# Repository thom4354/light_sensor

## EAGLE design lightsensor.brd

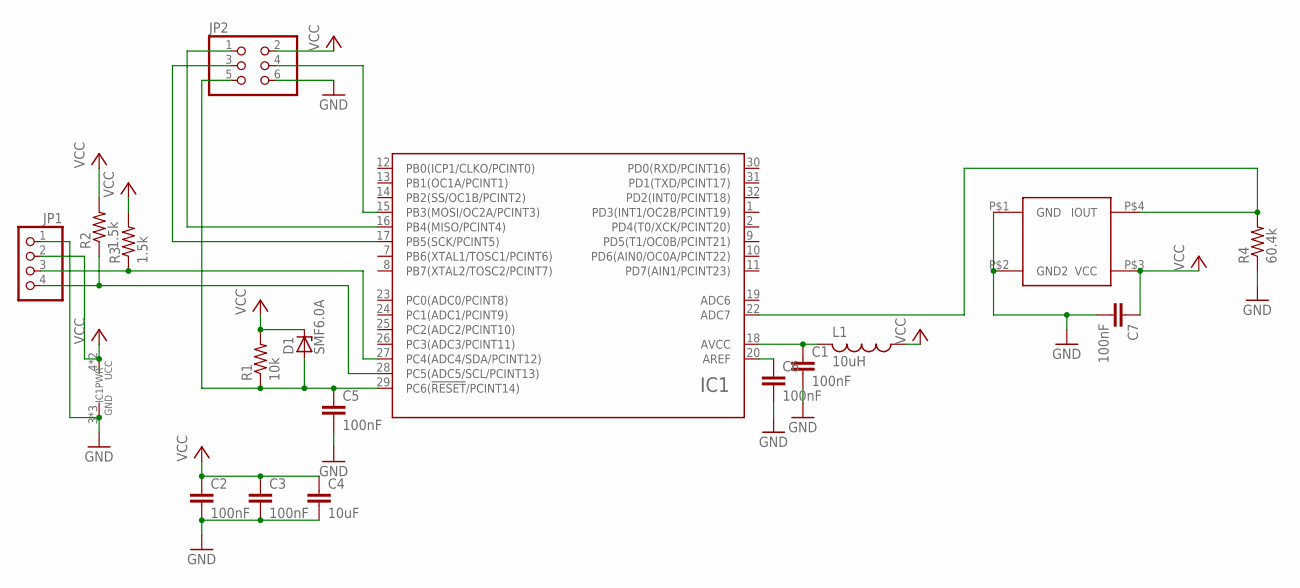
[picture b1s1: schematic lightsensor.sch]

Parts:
C1, C2, C3, C5, C6, C7: 100nF; C0402
C4: 10uF; C0603
D1: SMF6.0A; SOD123F
IC1: ATMEGA48/88/168/328-AU; TQFP32-08
JP1: PINHD-1X4; 1X04
JP2: PINHD-2X3; 2X03
L1: 10uH; L2012C
R1: 10k; R0402
R2, R3: 1.5k; R0402
R4: 60.4k; R0603
U$1: SFH5711

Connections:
GND: C1.2, C2.2, C3.2, C4.2, C5.2, C6.2, C7.2, IC1.3 (GND), IC1.5 (GND), IC1.21 (GND), JP1.1, JP2.6, R4.1, U$1.P$1 (GND), U$1.P$2 (GND2)
unnamed: C1.1, IC1.18 (AVCC), L1.2
unnamed: IC1.16 (PB4(MISO/PCINT4)), JP2.1
unnamed: IC1.17 (PB5(SCK/PCINT5)), JP2.3
unnamed: IC1.15 (PB3(MOSI/OC2A/PCINT3)), JP2.4
unnamed: C5.1, D1.A, IC1.29 (PC6(!RESET!/PCINT14)), JP2.5, R1.1
unnamed: C6.1, IC1.20 (AREF)
unnamed: IC1.27 (PC4(ADC4/SDA/PCINT12)), JP1.3, R3.1
unnamed: IC1.22 (ADC7), R4.2, U$1.P$4 (IOUT)
unnamed: IC1.28 (PC5(ADC5/SCL/PCINT13)), JP1.4, R2.1
VCC: C2.1, C3.1, C4.1, C7.1, D1.C, IC1.4 (UCC), IC1.6 (UCC), JP1.2, JP2.2, L1.1, R1.2, R2.2, R3.2, U$1.P$3 (VCC)

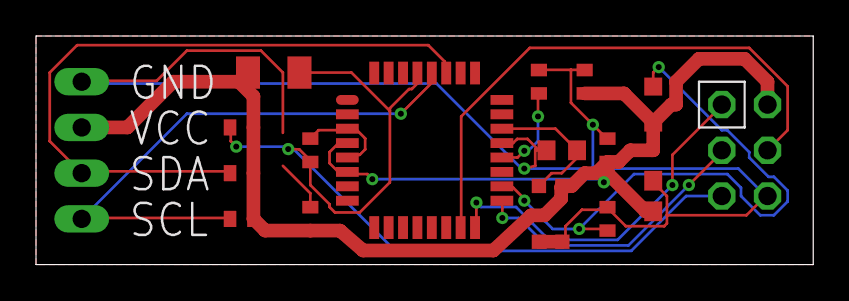
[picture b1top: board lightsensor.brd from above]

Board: 2 copper layers, 43.2 x 12.7 mm, 17 parts (0 on the bottom side), 11 nets.

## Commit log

2017-02-16 Added schematic screenshot
